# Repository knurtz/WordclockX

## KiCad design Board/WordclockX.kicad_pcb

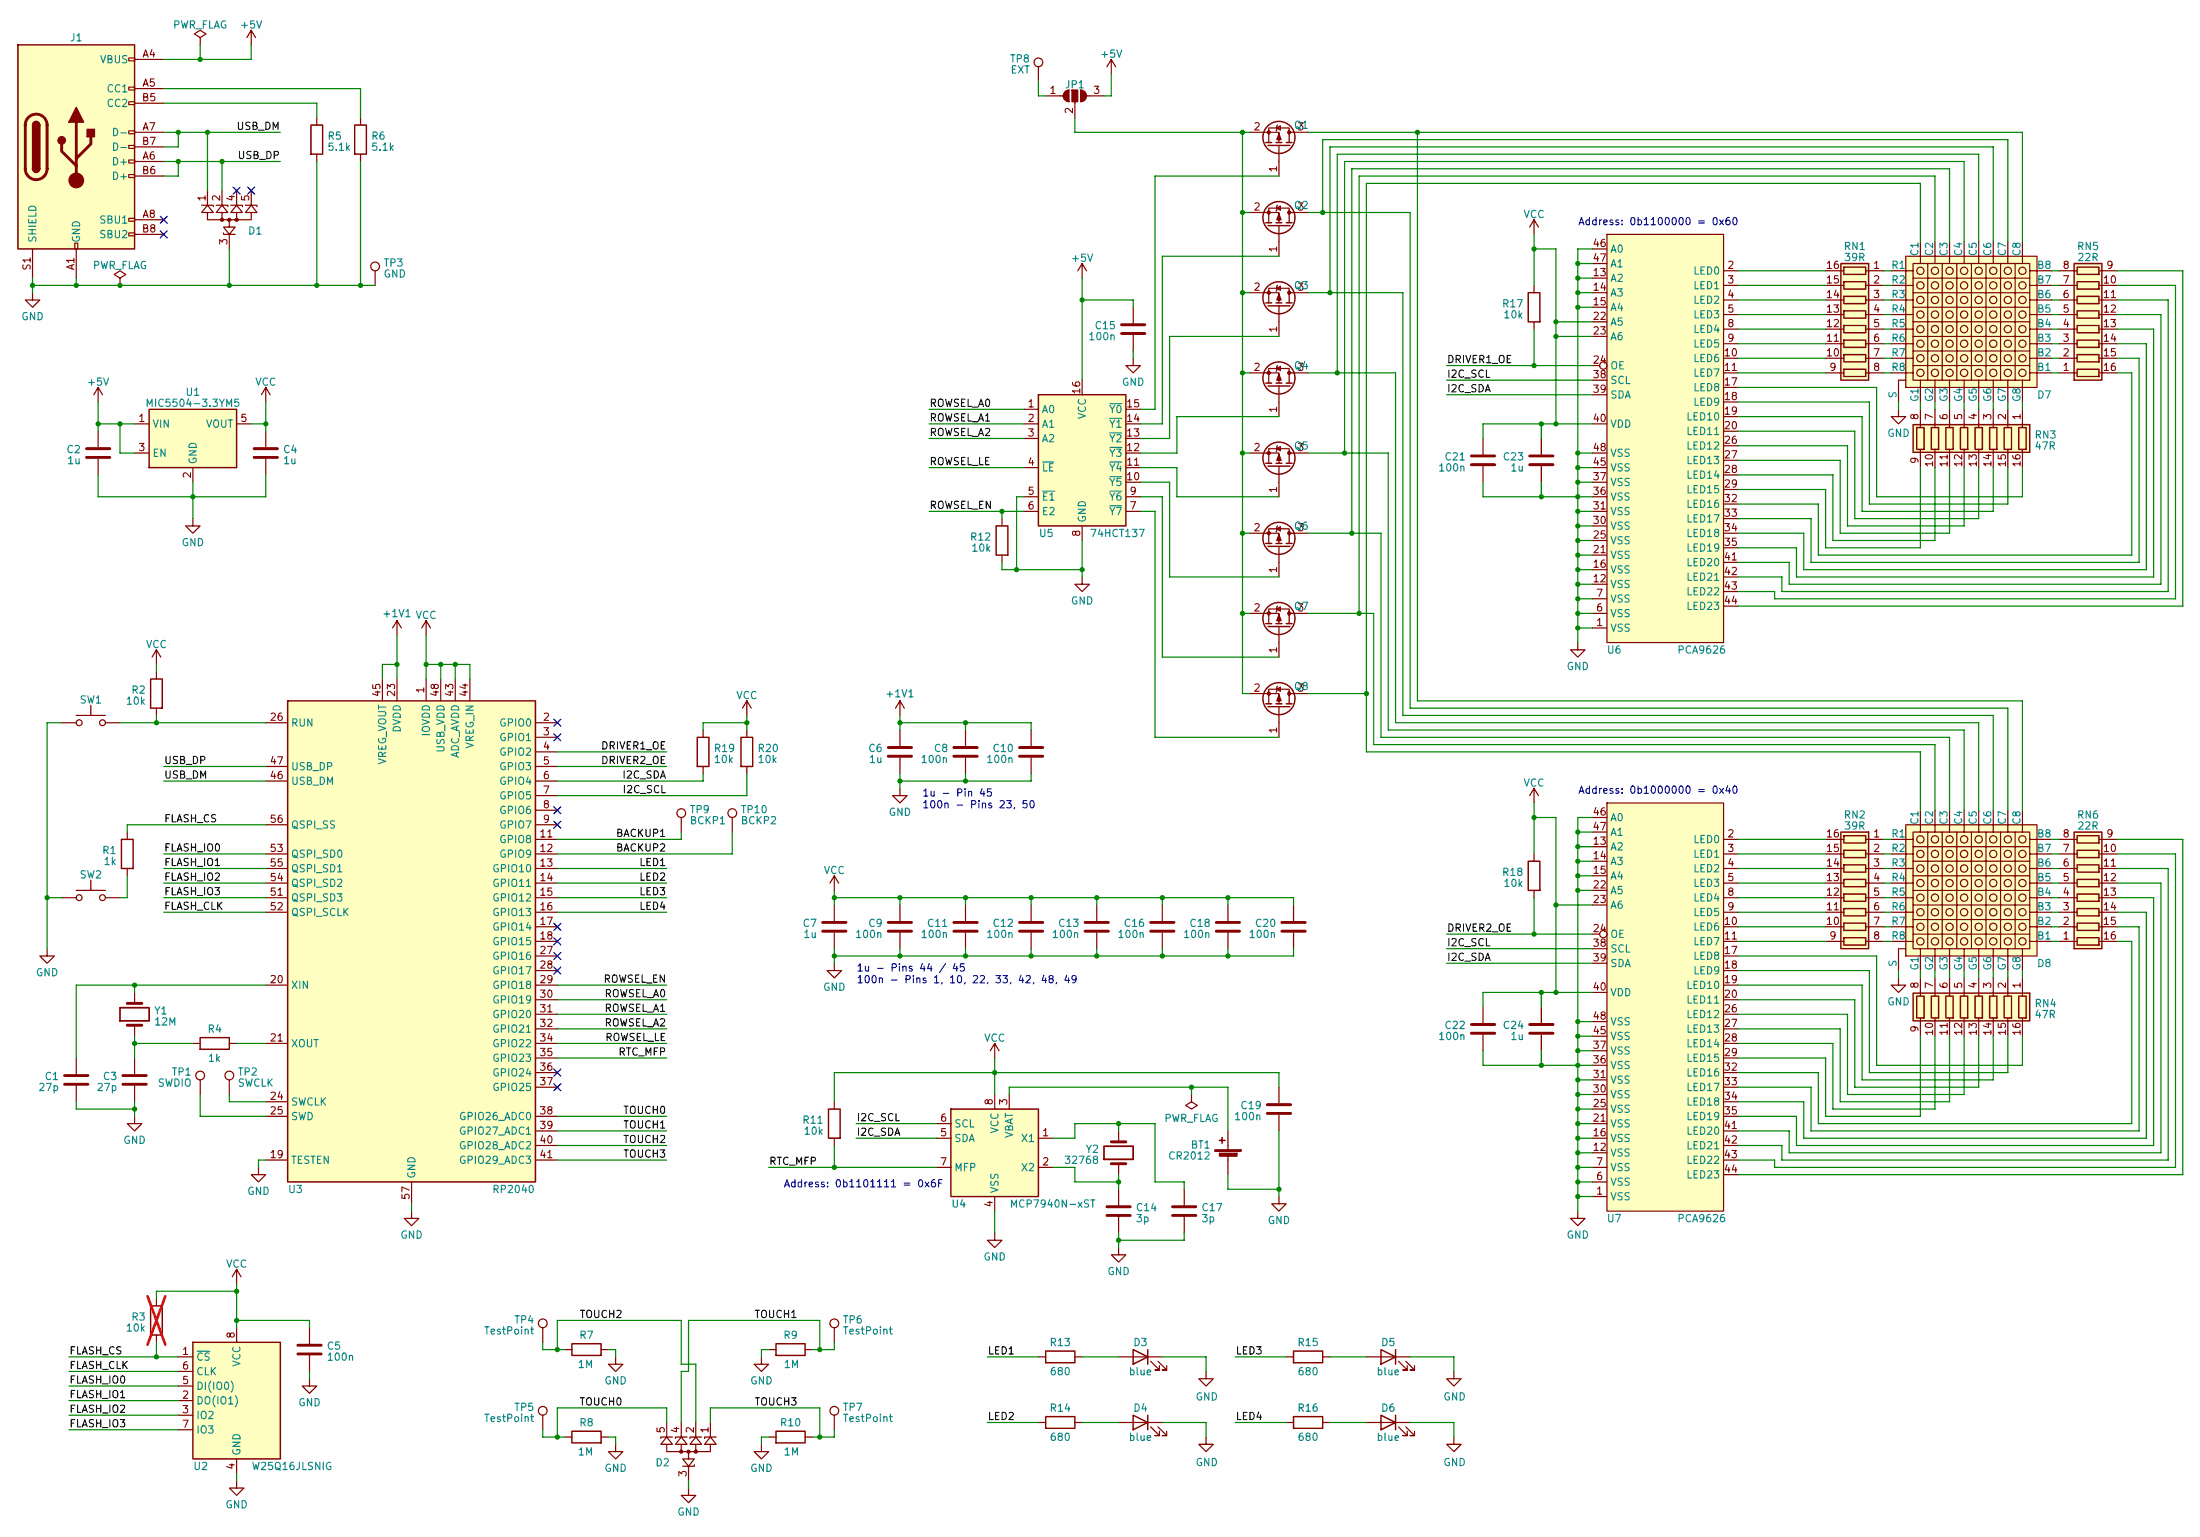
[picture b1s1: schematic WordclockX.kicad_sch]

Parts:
BT1: CR2012; BatteryHolder_MPD_BC2003_1x2032; Mouser 712-BAT-HLD-002-SMT
C1, C3: 27p; C_0603_1608Metric
C2, C4, C6, C7, C23, C24: 1u; C_0805_2012Metric
C5, C8, C9, C10, C11, C12, C13, C15, C16, C18, C19, C20, C21, C22: 100n; C_0603_1608Metric
C14, C17: 3p; C_0603_1608Metric
D1, D2: Diodes_UDFN-10_1.0x2.5mm_P0.5mm; Mouser 576-SP1064E-04UTG
D3, D4, D5, D6: blue; LED_0603_1608Metric; Mouser 710-150060BS75000
D7, D8: RGB2088-5; 2088RGB-5_no-holes
J1: USB_C_Receptacle_USB2.0; USB_C_Receptacle_GCT_USB4145
JP1: SolderJumper_3_Open; SolderJumper-3_P1.3mm_Open_RoundedPad1.0x1.5mm
Q1, Q2, Q3, Q4, Q5, Q6, Q7, Q8: SOT-23; Mouser 241-PJA3415AAUR100A1
R1, R4: 1k; R_0603_1608Metric
R2, R11, R12, R17, R18, R19, R20: 10k; R_0603_1608Metric
R3: 10k; R_0603_1608Metric; not fitted
R5, R6: 5.1k; R_0603_1608Metric
R7, R8, R9, R10: 1M; R_0603_1608Metric
R13, R14, R15, R16: 680; R_0603_1608Metric
RN1, RN2: 39R; R_Array_Convex_8x0602; Mouser 667-EXB-2HV390JV
RN3, RN4: 47R; R_Array_Convex_8x0602; Mouser 667-EXB-2HV470JV
RN5, RN6: 22R; R_Array_Convex_8x0602; Mouser 667-EXB-2HV220JV
SW1, SW2: SW_Push_Dual; SW_Push_1P1T_NO_CK_KSC6xxJ
TP1: SWDIO; TestPoint_Pad_1.0x1.0mm
TP2: SWCLK; TestPoint_Pad_1.0x1.0mm
TP3: GND; TestPoint_Pad_1.0x1.0mm
TP4, TP5, TP6, TP7: TestPoint; TestPoint_Pad_D4.0mm
TP8: EXT; TestPoint_Pad_1.0x1.0mm
TP9: BCKP1; TestPoint_Pad_1.0x1.0mm
TP10: BCKP2; TestPoint_Pad_1.0x1.0mm
U1: MIC5504-3.3YM5; SOT-23-5; Mouser 998-MIC5504-3.3YM5TR
U2: W25Q16JLSNIG; SOIC-8_3.9x4.9mm_P1.27mm; Mouser 454-W25Q16JLSNIG
U3: RP2040; QFN-56-1EP_7x7mm_P0.4mm_EP3.2x3.2mm
U4: MCP7940N-xST; TSSOP-8_4.4x3mm_P0.65mm; Mouser 579-MCP7940N-I/ST
U5: 74HCT137; SOIC-16_3.9x9.9mm_P1.27mm; Mouser 595-CD74HCT137MT
U6, U7: PCA9626; LQFP-48_7x7mm_P0.5mm
Y1: 12M; Crystal_SMD_5032-2Pin_5.0x3.2mm; Mouser 774-445C25D12M00000
Y2: 32768; Crystal_SMD_3215-2Pin_3.2x1.5mm; Mouser 628-SC32S-7PF20PPM

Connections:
+1V1: C6.1, C8.1, C10.1, U3.23 (DVDD), U3.45 (VREG_VOUT), U3.50 (DVDD)
+5V: C2.1, C15.1, J1.A4 (VBUS), J1.A9 (VBUS), J1.B4 (VBUS), J1.B9 (VBUS), JP1.3 (B), U1.1 (VIN), U1.3 (EN), U5.16 (VCC)
/BACKUP1: TP9.1, U3.11 (GPIO8)
/BACKUP2: TP10.1, U3.12 (GPIO9)
/DRIVER1_OE: R17.2, U3.4 (GPIO2), U6.24 (OE)
/DRIVER2_OE: R18.2, U3.5 (GPIO3), U7.24 (OE)
/FLASH_CLK: U2.6 (CLK), U3.52 (QSPI_SCLK)
/FLASH_CS: R1.1, R3.2, U2.1 (~CS), U3.56 (QSPI_SS)
/FLASH_IO0: U2.5 (DI(IO0)), U3.53 (QSPI_SD0)
/FLASH_IO1: U2.2 (DO(IO1)), U3.55 (QSPI_SD1)
/FLASH_IO2: U2.3 (IO2), U3.54 (QSPI_SD2)
/FLASH_IO3: U2.7 (IO3), U3.51 (QSPI_SD3)
/I2C_SCL: R20.2, U3.7 (GPIO5), U4.6 (SCL), U6.38 (SCL), U7.38 (SCL)
/I2C_SDA: R19.2, U3.6 (GPIO4), U4.5 (SDA), U6.39 (SDA), U7.39 (SDA)
/LED1: R13.2, U3.13 (GPIO10)
/LED2: R14.2, U3.14 (GPIO11)
/LED3: R15.2, U3.15 (GPIO12)
/LED4: R16.2, U3.16 (GPIO13)
/ROWSEL_A0: U3.30 (GPIO19), U5.1 (A0)
/ROWSEL_A1: U3.31 (GPIO20), U5.2 (A1)
/ROWSEL_A2: U3.32 (GPIO21), U5.3 (A2)
/ROWSEL_EN: R12.1, U3.29 (GPIO18), U5.6 (E2)
/ROWSEL_LE: U3.34 (GPIO22), U5.4 (~LE)
/RTC_MFP: R11.2, U3.35 (GPIO23), U4.7 (MFP)
/TOUCH0: D2.5 (Ch.4), D2.6 (Ch.4), R8.1, TP5.1, U3.38 (GPIO26_ADC0)
/TOUCH1: D2.4 (Ch.3), D2.7 (Ch.3), R9.1, TP6.1, U3.39 (GPIO27_ADC1)
/TOUCH2: D2.2 (Ch.2), D2.9 (Ch.2), R7.1, TP4.1, U3.40 (GPIO28_ADC2)
/TOUCH3: D2.1 (Ch.1), D2.10 (Ch.1), R10.1, TP7.1, U3.41 (GPIO29_ADC3)
/USB_DM: D1.1 (Ch.1), D1.10 (Ch.1), J1.A7 (D-), J1.B7 (D-), U3.46 (USB_DM)
/USB_DP: D1.2 (Ch.2), D1.9 (Ch.2), J1.A6 (D+), J1.B6 (D+), U3.47 (USB_DP)
GND: BT1.2 (-), C1.2, C2.2, C3.2, C4.2, C5.2, C6.2, C7.2, C8.2, C9.2, C10.2, C11.2, C12.2, C13.2, C14.2, C15.2, C16.2, C17.2, C18.2, C19.2, C20.2, C21.2, C22.2, C23.2, C24.2, D1.3 (GND), D1.8 (GND), D2.3 (GND), D2.8 (GND), D3.1 (K), D4.1 (K), D5.1 (K), D6.1 (K), D7.S, D8.S, J1.A1 (GND), J1.A12 (GND), J1.B1 (GND), J1.B12 (GND), J1.S1 (SHIELD), R5.2, R6.2, R7.2, R8.2, R9.2, R10.2, R12.2, SW1.1, SW2.1, TP3.1, U1.2 (GND), U2.4 (GND), U3.19 (TESTEN), U3.57 (GND), U4.4 (VSS), U5.5 (~E1), U5.8 (GND), U6.1 (VSS), U6.6 (VSS), U6.7 (VSS), U6.12 (VSS), U6.13 (A2), U6.14 (A3), U6.15 (A4), U6.16 (VSS), U6.21 (VSS), U6.25 (VSS), U6.30 (VSS), U6.31 (VSS), U6.36 (VSS), U6.37 (VSS), U6.45 (VSS), U6.46 (A0), U6.47 (A1), U6.48 (VSS), U7.1 (VSS), U7.6 (VSS), U7.7 (VSS), U7.12 (VSS), U7.13 (A2), U7.14 (A3), U7.15 (A4), U7.16 (VSS), U7.21 (VSS), U7.22 (A5), U7.25 (VSS), U7.30 (VSS), U7.31 (VSS), U7.36 (VSS), U7.37 (VSS), U7.45 (VSS), U7.46 (A0), U7.47 (A1), U7.48 (VSS)
unnamed: BT1.1 (+), U4.3 (VBAT)
unnamed: C3.1, R4.2, Y1.1
unnamed: D3.2 (A), R13.1
unnamed: D4.2 (A), R14.1
unnamed: D5.2 (A), R15.1
unnamed: D6.2 (A), R16.1
unnamed: D7.1 (B1), RN5.1 (R1.1)
unnamed: D7.2 (B2), RN5.2 (R2.1)
unnamed: D7.3 (B3), RN5.3 (R3.1)
unnamed: D7.4 (B4), RN5.4 (R4.1)
unnamed: D7.5 (B5), RN5.5 (R5.1)
unnamed: D7.6 (B6), RN5.6 (R6.1)
unnamed: D7.7 (B7), RN5.7 (R7.1)
unnamed: D7.8 (B8), RN5.8 (R8.1)
unnamed: D7.17 (C1), D8.17 (C1), Q8.3 (D)
unnamed: D7.18 (C2), D8.18 (C2), Q7.3 (D)
unnamed: D7.19 (C3), D8.19 (C3), Q6.3 (D)
unnamed: D7.20 (C4), D8.20 (C4), Q5.3 (D)
unnamed: D7.29 (C5), D8.29 (C5), Q4.3 (D)
unnamed: D7.30 (C6), D8.30 (C6), Q3.3 (D)
unnamed: D7.31 (C7), D8.31 (C7), Q2.3 (D)
unnamed: D7.32 (C8), D8.32 (C8), Q1.3 (D)
unnamed: D7.28 (G1), RN3.8 (R8.1)
unnamed: D7.27 (G2), RN3.7 (R7.1)
unnamed: D7.26 (G3), RN3.6 (R6.1)
unnamed: D7.25 (G4), RN3.5 (R5.1)
unnamed: D7.24 (G5), RN3.4 (R4.1)
unnamed: D7.23 (G6), RN3.3 (R3.1)
unnamed: D7.22 (G7), RN3.2 (R2.1)
unnamed: D7.21 (G8), RN3.1 (R1.1)
unnamed: D7.9 (R1), RN1.1 (R1.1)
unnamed: D7.10 (R2), RN1.2 (R2.1)
unnamed: D7.11 (R3), RN1.3 (R3.1)
unnamed: D7.12 (R4), RN1.4 (R4.1)
unnamed: D7.13 (R5), RN1.5 (R5.1)
unnamed: D7.14 (R6), RN1.6 (R6.1)
unnamed: D7.15 (R7), RN1.7 (R7.1)
unnamed: D7.16 (R8), RN1.8 (R8.1)
unnamed: D8.1 (B1), RN6.1 (R1.1)
unnamed: D8.2 (B2), RN6.2 (R2.1)
unnamed: D8.3 (B3), RN6.3 (R3.1)
unnamed: D8.4 (B4), RN6.4 (R4.1)
unnamed: D8.5 (B5), RN6.5 (R5.1)
unnamed: D8.6 (B6), RN6.6 (R6.1)
unnamed: D8.7 (B7), RN6.7 (R7.1)
unnamed: D8.8 (B8), RN6.8 (R8.1)
unnamed: D8.28 (G1), RN4.8 (R8.1)
unnamed: D8.27 (G2), RN4.7 (R7.1)
unnamed: D8.26 (G3), RN4.6 (R6.1)
unnamed: D8.25 (G4), RN4.5 (R5.1)
unnamed: D8.24 (G5), RN4.4 (R4.1)
unnamed: D8.23 (G6), RN4.3 (R3.1)
unnamed: D8.22 (G7), RN4.2 (R2.1)
unnamed: D8.21 (G8), RN4.1 (R1.1)
unnamed: D8.9 (R1), RN2.1 (R1.1)
unnamed: D8.10 (R2), RN2.2 (R2.1)
unnamed: D8.11 (R3), RN2.3 (R3.1)
unnamed: D8.12 (R4), RN2.4 (R4.1)
unnamed: D8.13 (R5), RN2.5 (R5.1)
unnamed: D8.14 (R6), RN2.6 (R6.1)
unnamed: D8.15 (R7), RN2.7 (R7.1)
unnamed: D8.16 (R8), RN2.8 (R8.1)
unnamed: J1.A5 (CC1), R6.1
unnamed: J1.B5 (CC2), R5.1
unnamed: JP1.1 (A), TP8.1
unnamed: JP1.2 (C), Q1.2 (S), Q2.2 (S), Q3.2 (S), Q4.2 (S), Q5.2 (S), Q6.2 (S), Q7.2 (S), Q8.2 (S)
unnamed: Q1.1 (G), U5.15 (~Y0)
unnamed: Q2.1 (G), U5.14 (~Y1)
unnamed: Q3.1 (G), U5.13 (~Y2)
unnamed: Q4.1 (G), U5.12 (~Y3)
unnamed: Q5.1 (G), U5.11 (~Y4)
unnamed: Q6.1 (G), U5.10 (~Y5)
unnamed: Q7.1 (G), U5.9 (~Y6)
unnamed: Q8.1 (G), U5.7 (~Y7)
unnamed: R1.2, SW2.2
unnamed: RN1.16 (R1.2), U6.2 (LED0)
unnamed: RN1.15 (R2.2), U6.3 (LED1)
unnamed: RN1.14 (R3.2), U6.4 (LED2)
unnamed: RN1.13 (R4.2), U6.5 (LED3)
unnamed: RN1.12 (R5.2), U6.8 (LED4)
unnamed: RN1.11 (R6.2), U6.9 (LED5)
unnamed: RN1.10 (R7.2), U6.10 (LED6)
unnamed: RN1.9 (R8.2), U6.11 (LED7)
unnamed: RN2.16 (R1.2), U7.2 (LED0)
unnamed: RN2.15 (R2.2), U7.3 (LED1)
unnamed: RN2.14 (R3.2), U7.4 (LED2)
unnamed: RN2.13 (R4.2), U7.5 (LED3)
unnamed: RN2.12 (R5.2), U7.8 (LED4)
unnamed: RN2.11 (R6.2), U7.9 (LED5)
unnamed: RN2.10 (R7.2), U7.10 (LED6)
unnamed: RN2.9 (R8.2), U7.11 (LED7)
unnamed: RN3.16 (R1.2), U6.17 (LED8)
unnamed: RN3.15 (R2.2), U6.18 (LED9)
unnamed: RN3.14 (R3.2), U6.19 (LED10)
unnamed: RN3.13 (R4.2), U6.20 (LED11)
unnamed: RN3.12 (R5.2), U6.26 (LED12)
unnamed: RN3.11 (R6.2), U6.27 (LED13)
unnamed: RN3.10 (R7.2), U6.28 (LED14)
unnamed: RN3.9 (R8.2), U6.29 (LED15)
unnamed: RN4.16 (R1.2), U7.17 (LED8)
unnamed: RN4.15 (R2.2), U7.18 (LED9)
unnamed: RN4.14 (R3.2), U7.19 (LED10)
unnamed: RN4.13 (R4.2), U7.20 (LED11)
unnamed: RN4.12 (R5.2), U7.26 (LED12)
unnamed: RN4.11 (R6.2), U7.27 (LED13)
unnamed: RN4.10 (R7.2), U7.28 (LED14)
unnamed: RN4.9 (R8.2), U7.29 (LED15)
unnamed: RN5.16 (R1.2), U6.32 (LED16)
unnamed: RN5.15 (R2.2), U6.33 (LED17)
unnamed: RN5.14 (R3.2), U6.34 (LED18)
unnamed: RN5.13 (R4.2), U6.35 (LED19)
unnamed: RN5.12 (R5.2), U6.41 (LED20)
unnamed: RN5.11 (R6.2), U6.42 (LED21)
unnamed: RN5.10 (R7.2), U6.43 (LED22)
unnamed: RN5.9 (R8.2), U6.44 (LED23)
unnamed: RN6.16 (R1.2), U7.32 (LED16)
unnamed: RN6.15 (R2.2), U7.33 (LED17)
unnamed: RN6.14 (R3.2), U7.34 (LED18)
unnamed: RN6.13 (R4.2), U7.35 (LED19)
unnamed: RN6.12 (R5.2), U7.41 (LED20)
unnamed: RN6.11 (R6.2), U7.42 (LED21)
unnamed: RN6.10 (R7.2), U7.43 (LED22)
unnamed: RN6.9 (R8.2), U7.44 (LED23)
unnamed: R2.2, SW1.2, U3.26 (RUN)
unnamed: TP2.1, U3.24 (SWCLK)
unnamed: TP1.1, U3.25 (SWD)
unnamed: C1.1, U3.20 (XIN), Y1.2
unnamed: R4.1, U3.21 (XOUT)
unnamed: C17.1, U4.1 (X1), Y2.2
unnamed: C14.1, U4.2 (X2), Y2.1
VCC: C4.1, C5.1, C7.1, C9.1, C11.1, C12.1, C13.1, C16.1, C18.1, C19.1, C20.1, C21.1, C22.1, C23.1, C24.1, R2.1, R3.1, R11.1, R17.1, R18.1, R19.1, R20.1, U1.5 (VOUT), U2.8 (VCC), U3.1 (IOVDD), U3.10 (IOVDD), U3.22 (IOVDD), U3.33 (IOVDD), U3.42 (IOVDD), U3.43 (ADC_AVDD), U3.44 (VREG_IN), U3.48 (USB_VDD), U3.49 (IOVDD), U4.8 (VCC), U6.22 (A5), U6.23 (A6), U6.40 (VDD), U7.23 (A6), U7.40 (VDD)

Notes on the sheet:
Address: 0b1000000 = 0x40
1u - Pin 45 100n - Pins 23, 50
1u - Pins 44 / 45 100n - Pins 1, 10, 22, 33, 42, 48, 49
Address: 0b1101111 = 0x6F
Address: 0b1100000 = 0x60

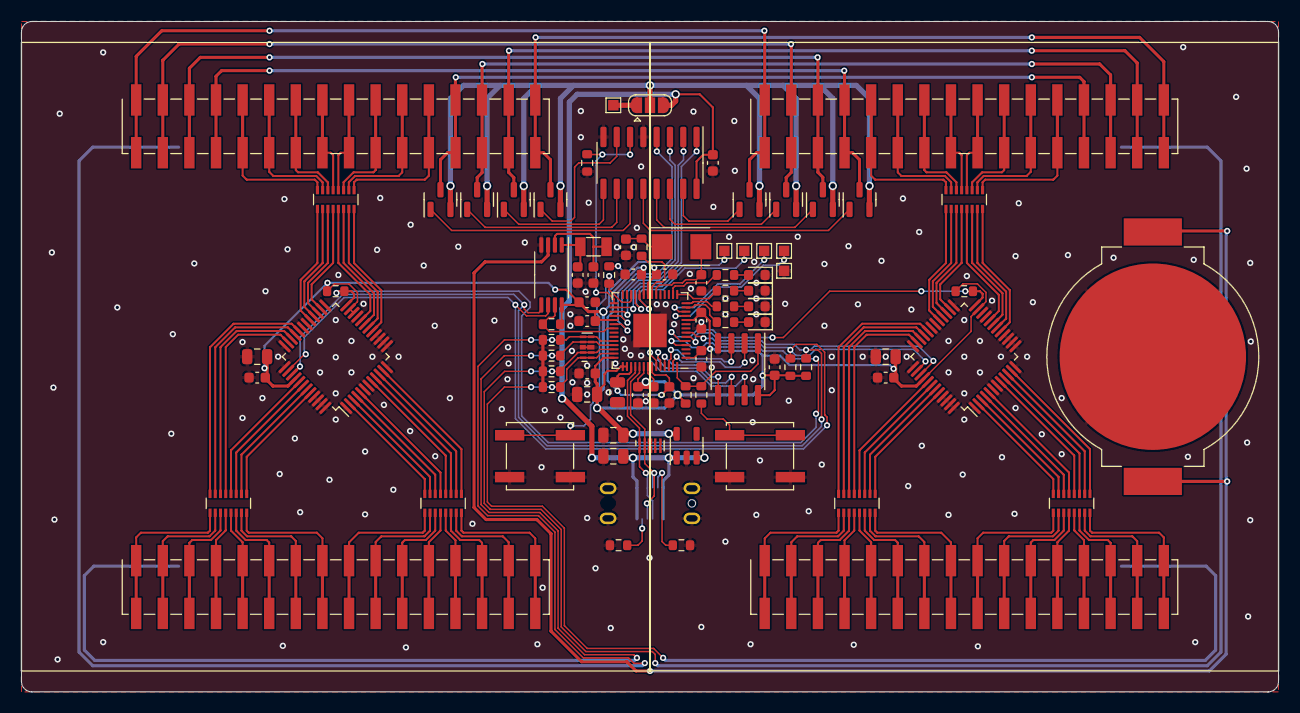
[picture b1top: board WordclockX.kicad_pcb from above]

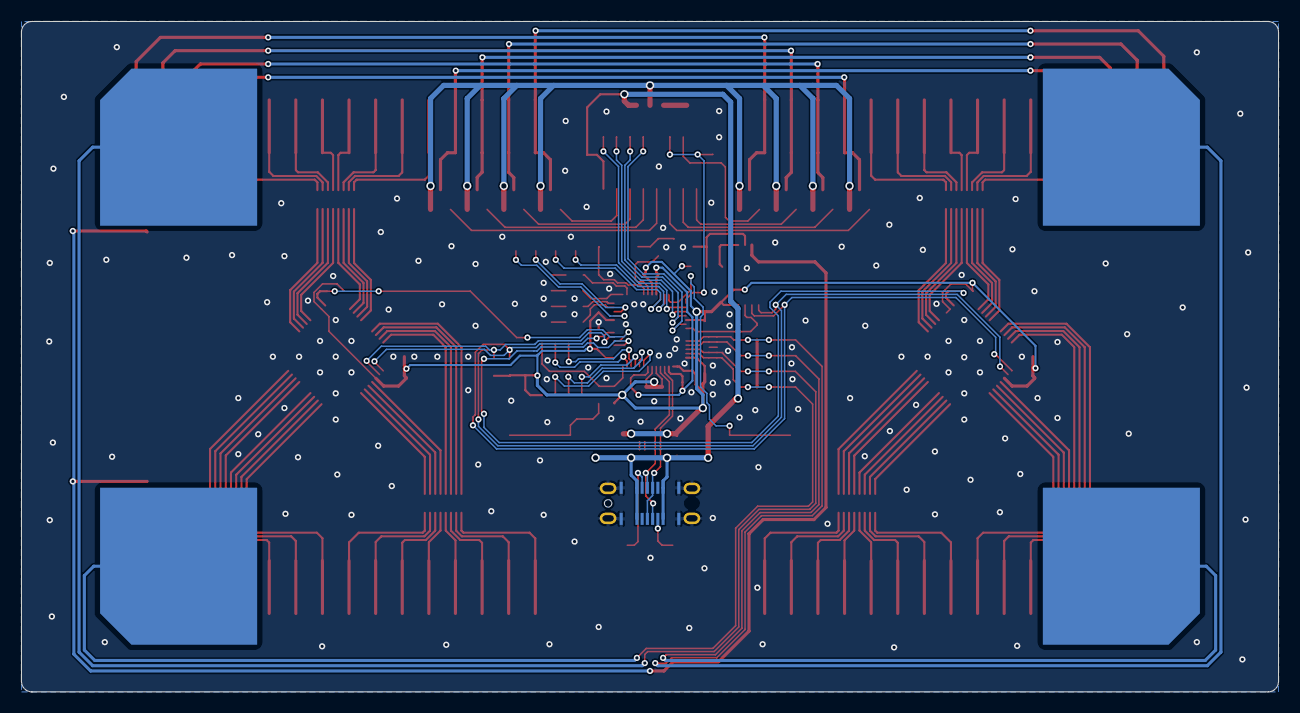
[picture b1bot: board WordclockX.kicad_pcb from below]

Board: 2 copper layers, 120.0 x 64.0 mm, 90 parts (5 on the bottom side), 162 nets.

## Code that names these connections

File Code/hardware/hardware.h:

#ifndef HARDWARE_H
#define HARDWARE_H

#include "pico/stdlib.h"

#define kHz * 1000
#define MHz * 1000 * 1000

// Generic IOs
#define LED1                    10
#define LED2                    11
#define LED3                    12
#define LED4                    13

// I2C
#define I2C_SDA                 4
#define I2C_SCL                 5

// Row selection
#define ROWSEL_A0               19
#define ROWSEL_A1               20
#define ROWSEL_A2               21

#define ROWSEL_LATCH            22
#define ROWSEL_EN               18

// Column selection
#define DRIVER1_NOE              2
#define DRIVER2_NOE              3

// Initializes all GPIOs
bool Hardware_Init(void);

#endif /* HARDWARE_H */

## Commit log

2023-04-30 Let's start with some datasheets
2023-04-30 16x8 letter array for word clock
2023-04-30 First version of schematic almost done.
2023-04-30 Added gitignore, removed unnecessary files from repo
2023-05-01 Some additions to the schematic
2023-05-02 Sized our board and placed LEDs to final location
2023-05-03 Added capacitors and pin assignments, also new footprint for LED array without holes
2023-05-04 Placed some resistors
2023-05-05 Started adding DC/DC converter for LED supply
2023-05-08 Finished adding voltage regulators
2023-05-08 Removed regulators again, probably overkill
2023-05-08 Replaced individual resistors with resistor arrays
2023-05-08 Added product links and footprints to resistor arrays
2023-06-05 Assigned missing footprints
2023-06-09 Placement of components done
2023-06-09 Most of the routing done, I2C pullups missing!
2023-06-11 Routing almost done. Only touch buttons and battery supply missing.
2023-06-21 All routing done
2023-06-25 Finished board for production
2023-06-29 Added base code for RP2040 project
2023-07-08 Added interactive HTML BOM
2023-07-08 Base code running LEDs
2023-07-14 Added code for status LED and I2C scan
2023-07-14 Rescued board file from old commit
2023-07-17 RTC works
2023-07-17 Added some code for row selection
2023-07-18 LED matrix lit up
2023-07-19 Added pixel framebuffer
2023-07-20 Added more test code for matrix display
2023-07-25 Matrix works without burning up, added HSV2RGB code from someone else
2024-05-24 Simple number counting
